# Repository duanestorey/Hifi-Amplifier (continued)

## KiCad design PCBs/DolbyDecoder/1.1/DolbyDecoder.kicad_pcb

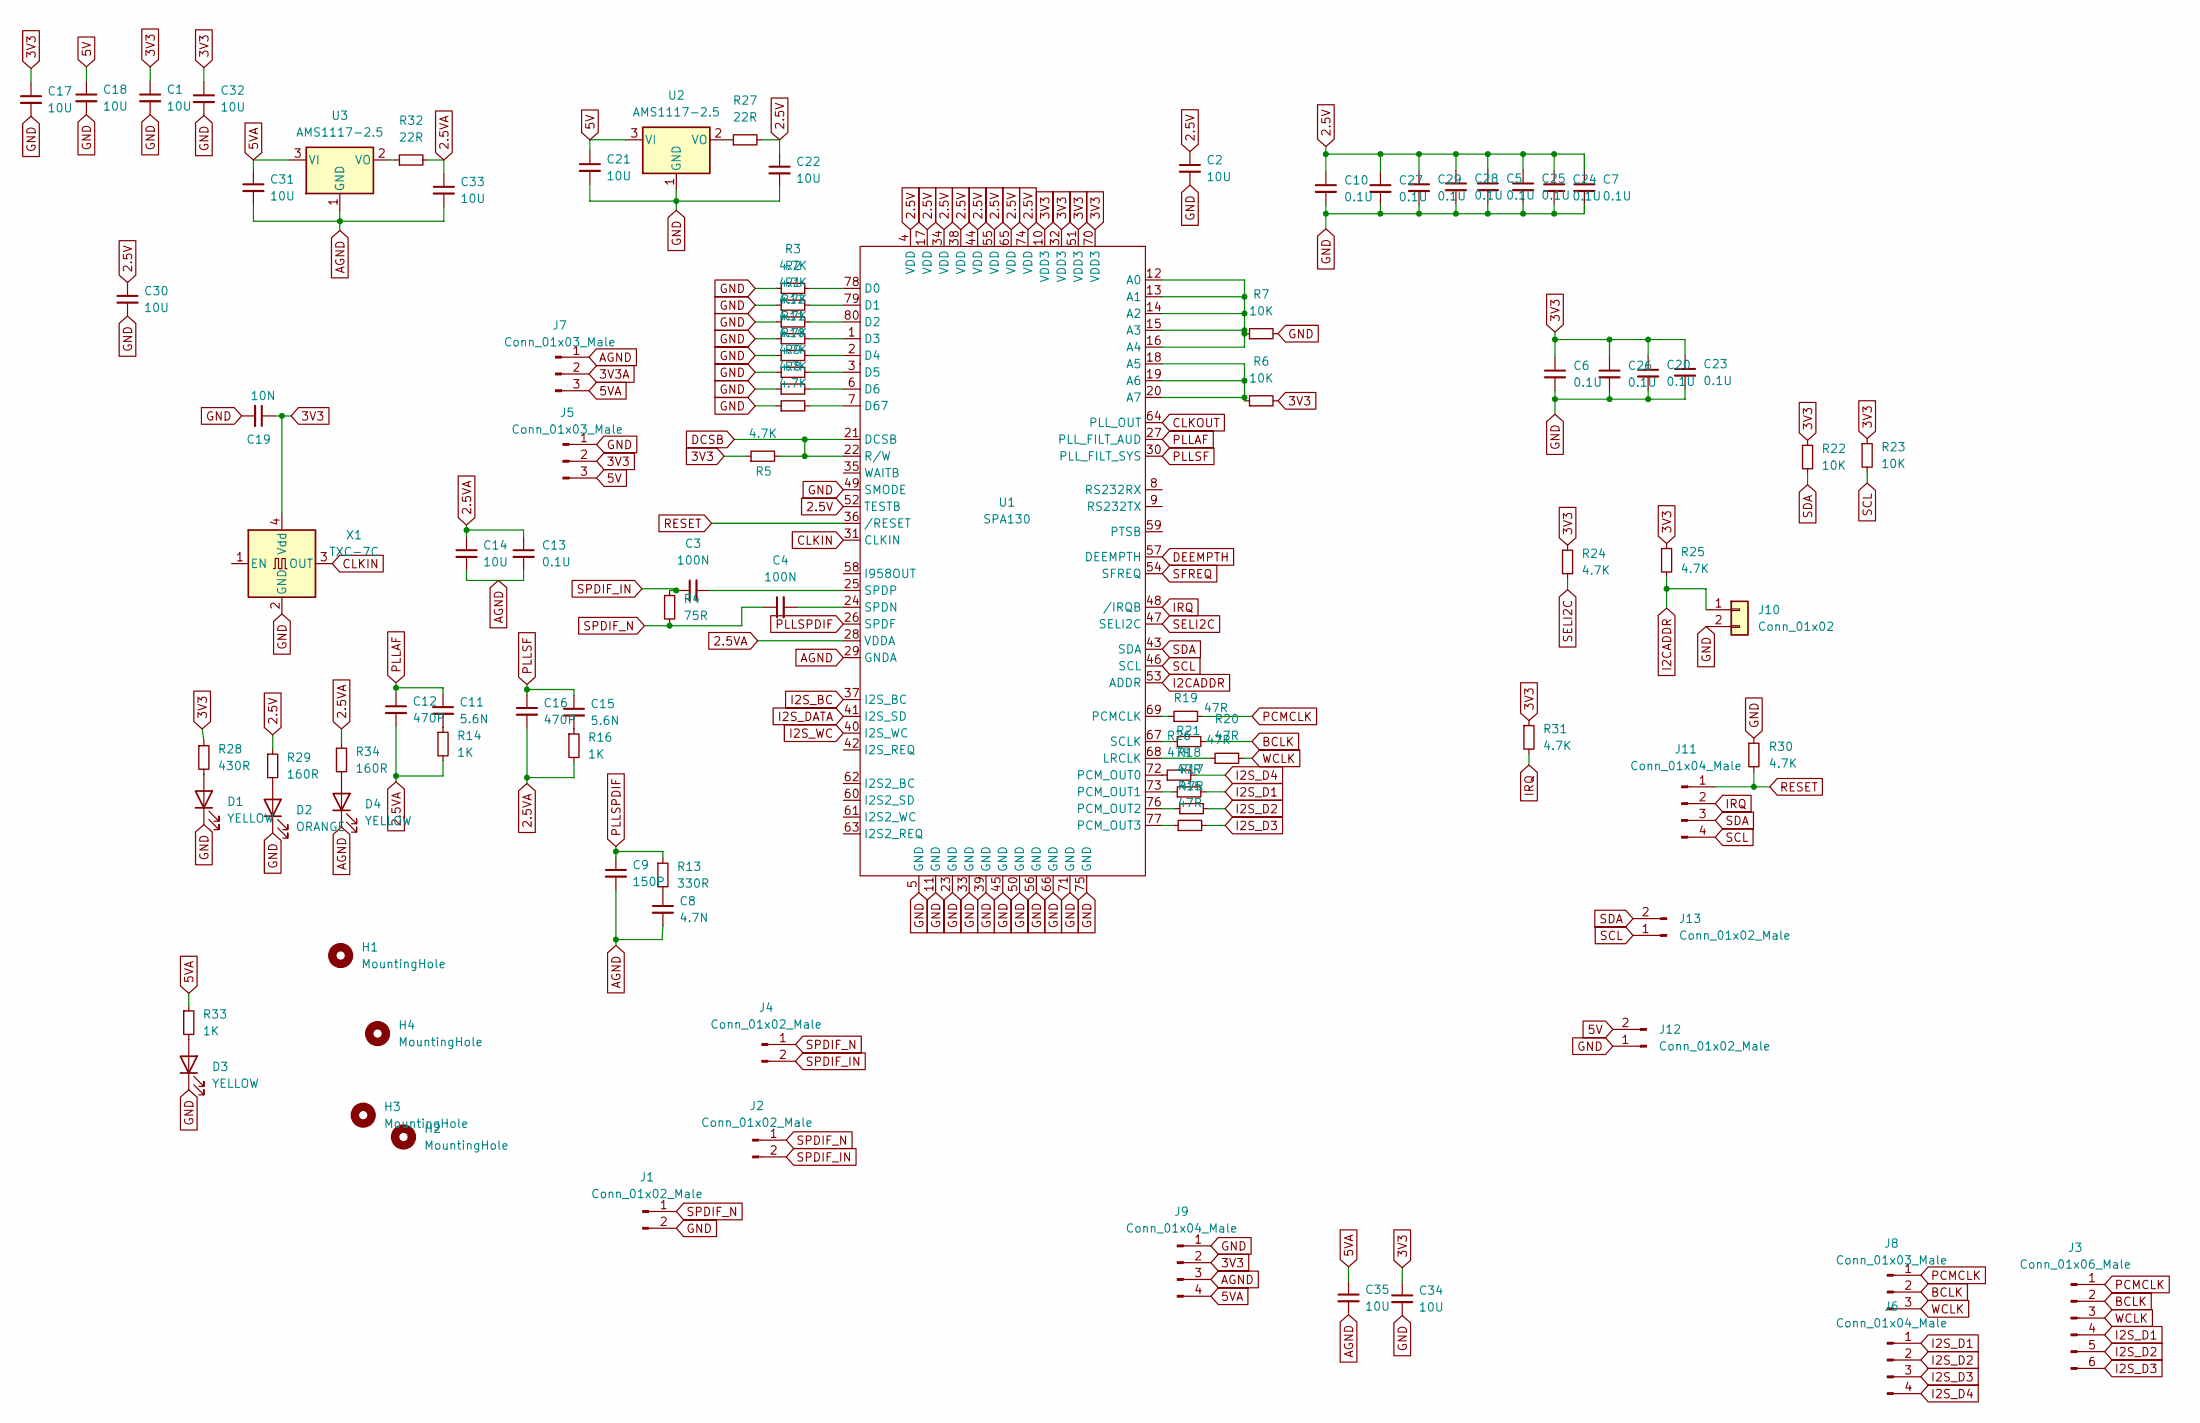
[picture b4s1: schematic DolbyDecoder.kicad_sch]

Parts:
C1, C2, C17, C18, C22, C30, C32, C33, C34, C35: 10U; C_1206_3216Metric_Pad1.33x1.80mm_HandSolder
C3, C4: 100N; C_0805_2012Metric_Pad1.18x1.45mm_HandSolder
C5, C6, C7, C10, C13, C20, C23, C24, C25, C26, C27, C28, C29: 0.1U; C_0603_1608Metric_Pad1.08x0.95mm_HandSolder
C8: 4.7N; C_0805_2012Metric_Pad1.18x1.45mm_HandSolder
C9: 150P; C_0805_2012Metric_Pad1.18x1.45mm_HandSolder
C11, C15: 5.6N; C_0805_2012Metric_Pad1.18x1.45mm_HandSolder
C12, C16: 470P; C_0805_2012Metric_Pad1.18x1.45mm_HandSolder
C14, C21, C31: 10U; C_0805_2012Metric_Pad1.18x1.45mm_HandSolder
C19: 10N; C_0603_1608Metric_Pad1.08x0.95mm_HandSolder
D1, D3, D4: YELLOW; LED_0805_2012Metric_Pad1.15x1.40mm_HandSolder
D2: ORANGE; LED_0805_2012Metric_Pad1.15x1.40mm_HandSolder
H1, H2, H3, H4: MountingHole; MountingHole_3.2mm_M3
J1, J2: Conn_01x02_Male; PinHeader_1x02_P2.54mm_Vertical
J3: Conn_01x06_Male; PinHeader_1x06_P2.54mm_Vertical
J4, J12, J13: Conn_01x02_Male; JST_PH_B2B-PH-K_1x02_P2.00mm_Vertical
J5, J7, J8: Conn_01x03_Male; JST_PH_B3B-PH-K_1x03_P2.00mm_Vertical
J6, J9, J11: Conn_01x04_Male; JST_PH_B4B-PH-K_1x04_P2.00mm_Vertical
J10: Conn_01x02; PinHeader_1x02_P2.54mm_Vertical
R1, R2, R3, R5, R8, R9, R10, R11, R12, R24, R25, R30, R31: 4.7K; R_0603_1608Metric_Pad0.98x0.95mm_HandSolder
R4: 75R; R_0603_1608Metric_Pad0.98x0.95mm_HandSolder
R6, R7, R22, R23: 10K; R_0603_1608Metric_Pad0.98x0.95mm_HandSolder
R13: 330R; R_0603_1608Metric_Pad0.98x0.95mm_HandSolder
R14, R16, R33: 1K; R_0603_1608Metric_Pad0.98x0.95mm_HandSolder
R15, R17, R18, R19, R20, R21, R26: 47R; R_0805_2012Metric_Pad1.20x1.40mm_HandSolder
R27, R32: 22R; R_0805_2012Metric_Pad1.20x1.40mm_HandSolder
R28: 430R; R_0603_1608Metric_Pad0.98x0.95mm_HandSolder
R29, R34: 160R; R_0603_1608Metric_Pad0.98x0.95mm_HandSolder
U1: SPA130; LQFP-80_14x14mm_P0.65mm
U2, U3: AMS1117-2.5; SOT-223
X1: TXC-7C; Oscillator_SMD_EuroQuartz_XO32-4Pin_3.2x2.5mm_HandSoldering

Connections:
2.5V: C2.1, C5.1, C7.1, C10.1, C22.1, C24.1, C25.1, C27.1, C28.1, C29.1, C30.1, R27.2, R29.1, U1.4 (VDD), U1.17 (VDD), U1.34 (VDD), U1.38 (VDD), U1.44 (VDD), U1.52 (TESTB), U1.55 (VDD), U1.65 (VDD), U1.74 (VDD)
2.5VA: C12.2, C13.1, C14.1, C16.2, C33.1, R14.2, R16.2, R32.2, R34.1, U1.28 (VDDA)
3V3: C1.1, C6.1, C17.1, C19.1, C20.1, C23.1, C26.1, C32.1, C34.1, J5.2, J9.2, R5.1, R6.2, R22.1, R23.1, R24.1, R25.1, R28.1, R31.1, U1.10 (VDD3), U1.32 (VDD3), U1.51 (VDD3), U1.70 (VDD3), X1.4 (Vdd)
3V3A: J7.2
5V: C18.1, C21.1, J5.3, J12.2, U2.3 (VI)
5VA: C31.1, C35.1, J7.3, J9.4, R33.1, U3.3 (VI)
AGND: C8.2, C9.2, C13.2, C14.2, C31.2, C33.2, C35.2, D4.1 (K), J7.1, J9.3, U1.29 (GNDA), U3.1 (GND)
BCLK: J3.2, J8.2, R21.2
CLKIN: U1.31 (CLKIN), X1.3 (OUT)
CLKOUT: U1.64 (PLL_OUT)
DCSB: R5.2, U1.21 (DCSB), U1.22 (R/W)
DEEMPTH: U1.57 (DEEMPTH)
GND: C1.2, C2.2, C5.2, C6.2, C7.2, C10.2, C17.2, C18.2, C19.2, C20.2, C21.2, C22.2, C23.2, C24.2, C25.2, C26.2, C27.2, C28.2, C29.2, C30.2, C32.2, C34.2, D1.1 (K), D2.1 (K), D3.1 (K), J1.2, J5.1, J9.1, J10.2, J12.1, R1.1, R2.1, R3.1, R7.2, R8.1, R9.1, R10.1, R11.1, R12.1, R30.1, U1.5 (GND), U1.11 (GND), U1.23 (GND), U1.33 (GND), U1.39 (GND), U1.45 (GND), U1.49 (SMODE), U1.50 (GND), U1.56 (GND), U1.66 (GND), U1.71 (GND), U1.75 (GND), U2.1 (GND), X1.2 (GND)
I2CADDR: J10.1, R25.2, U1.53 (ADDR)
I2S_BC: U1.37 (I2S_BC)
I2S_D1: J3.4, J6.1, R18.2
I2S_D2: J3.5, J6.2, R17.2
I2S_D3: J3.6, J6.3, R15.2
I2S_D4: J6.4, R26.2
I2S_DATA: U1.41 (I2S_SD)
I2S_WC: U1.40 (I2S_WC)
IRQ: J11.2, R31.2, U1.48 (/IRQB)
unnamed: C8.1, R13.2
unnamed: C11.2, R14.1
unnamed: C15.2, R16.1
unnamed: D1.2 (A), R28.2
unnamed: D2.2 (A), R29.2
unnamed: D3.2 (A), R33.2
unnamed: D4.2 (A), R34.2
unnamed: R7.1, U1.12 (A0), U1.13 (A1), U1.14 (A2), U1.15 (A3), U1.16 (A4)
unnamed: R6.1, U1.18 (A5), U1.19 (A6), U1.20 (A7)
unnamed: R3.2, U1.78 (D0)
unnamed: R2.2, U1.79 (D1)
unnamed: R1.2, U1.80 (D2)
unnamed: R12.2, U1.1 (D3)
unnamed: R11.2, U1.2 (D4)
unnamed: R10.2, U1.3 (D5)
unnamed: R9.2, U1.6 (D6)
unnamed: R8.2, U1.7 (D67)
unnamed: R20.1, U1.68 (LRCLK)
unnamed: R19.1, U1.69 (PCMCLK)
unnamed: R26.1, U1.72 (PCM_OUT0)
unnamed: R18.1, U1.73 (PCM_OUT1)
unnamed: R17.1, U1.76 (PCM_OUT2)
unnamed: R15.1, U1.77 (PCM_OUT3)
unnamed: R21.1, U1.67 (SCLK)
unnamed: C4.2, U1.24 (SPDN)
unnamed: C3.2, U1.25 (SPDP)
unnamed: R27.1, U2.2 (VO)
unnamed: R32.1, U3.2 (VO)
PCMCLK: J3.1, J8.1, R19.2
PLLAF: C11.1, C12.1, U1.27 (PLL_FILT_AUD)
PLLSF: C15.1, C16.1, U1.30 (PLL_FILT_SYS)
PLLSPDIF: C9.1, R13.1, U1.26 (SPDF)
RESET: J11.1, R30.2, U1.36 (/RESET)
SCL: J11.4, J13.1, R23.2, U1.46 (SCL)
SDA: J11.3, J13.2, R22.2, U1.43 (SDA)
SELI2C: R24.2, U1.47 (SELI2C)
SFREQ: U1.54 (SFREQ)
SPDIF_IN: C3.1, J2.2, J4.2, R4.1
SPDIF_N: C4.1, J1.1, J2.1, J4.1, R4.2
WCLK: J3.3, J8.3, R20.2

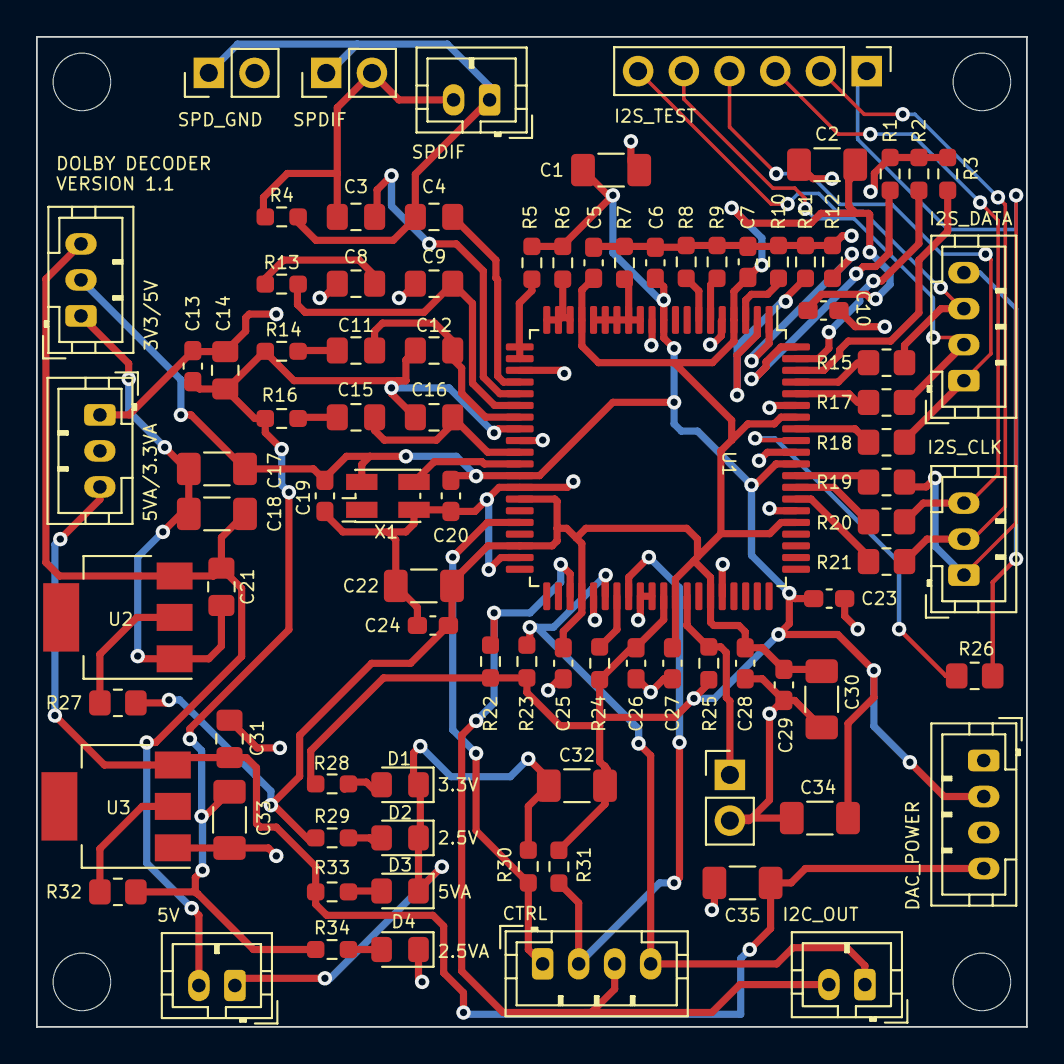
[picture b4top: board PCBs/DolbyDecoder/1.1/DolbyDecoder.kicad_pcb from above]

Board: 2 copper layers, 55.0 x 55.0 mm, 94 parts (0 on the bottom side), 55 nets.

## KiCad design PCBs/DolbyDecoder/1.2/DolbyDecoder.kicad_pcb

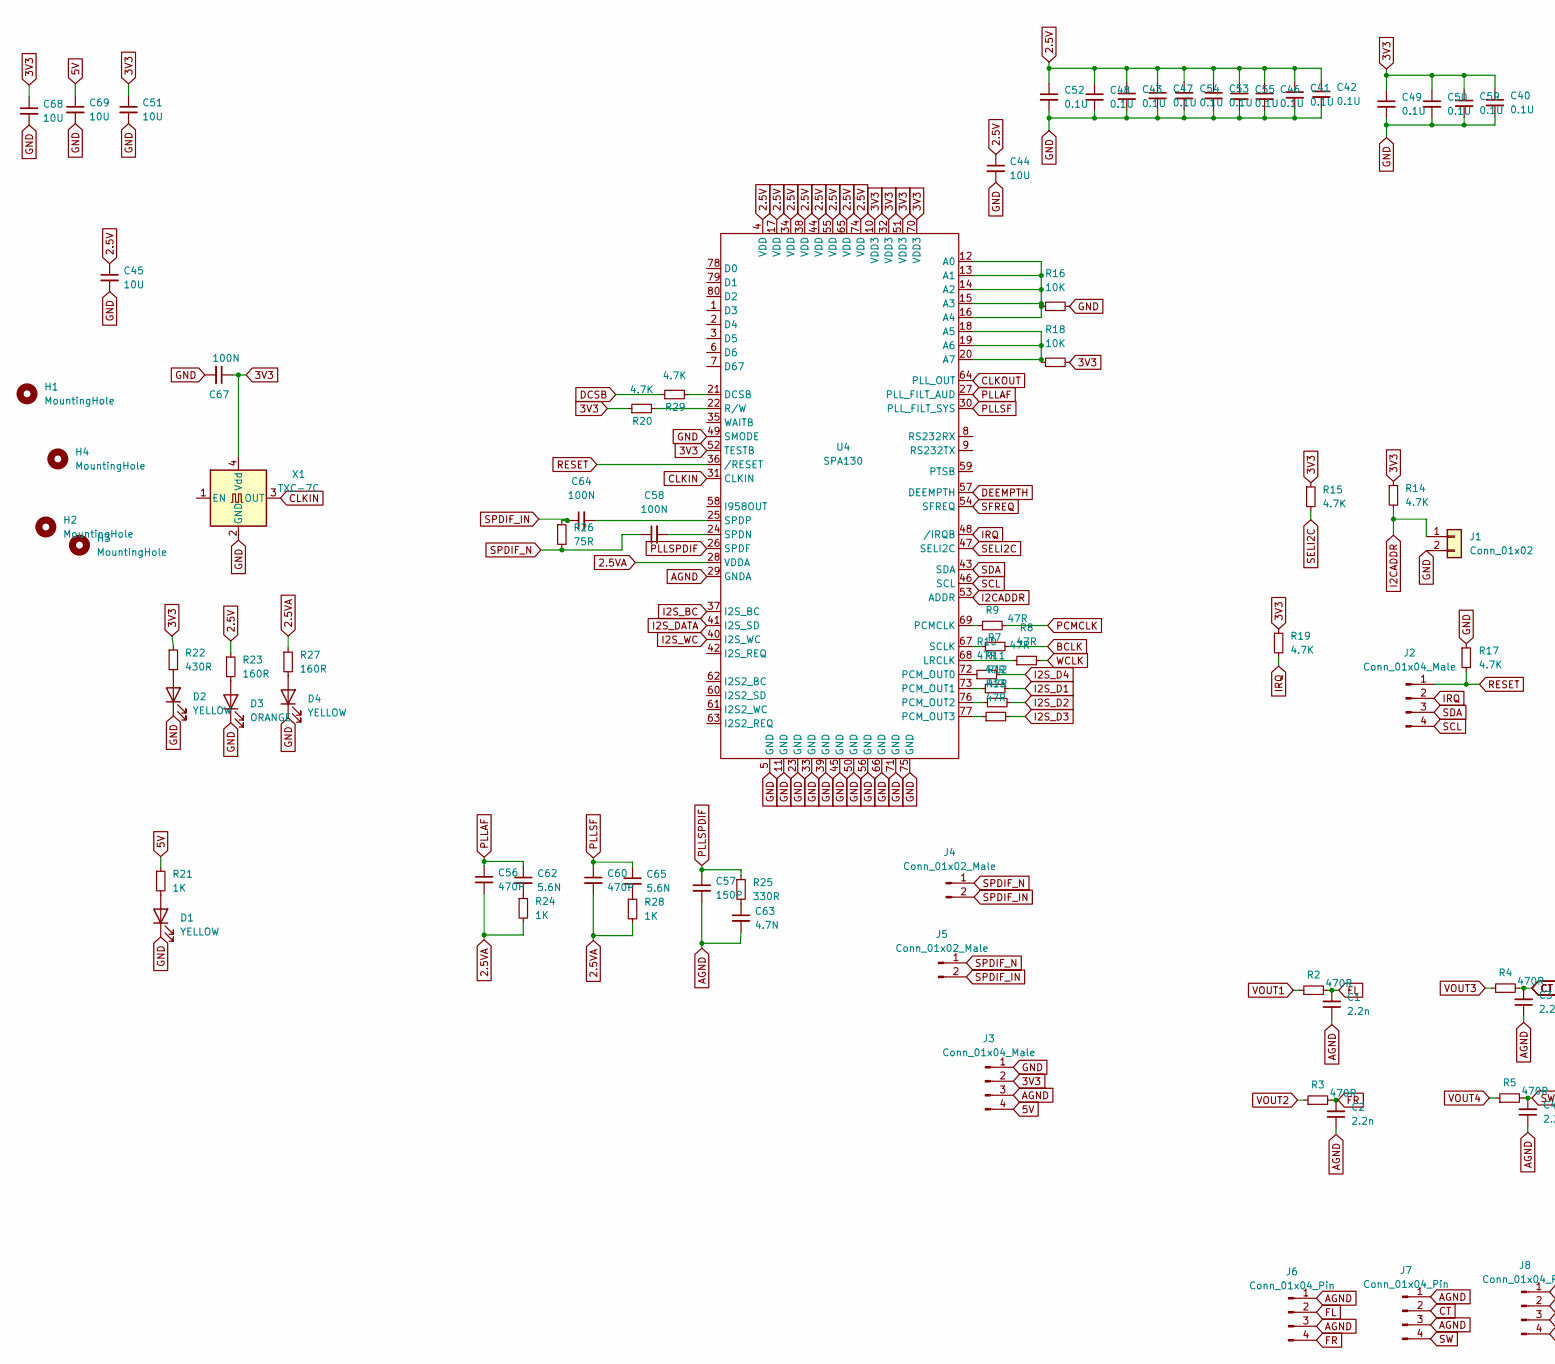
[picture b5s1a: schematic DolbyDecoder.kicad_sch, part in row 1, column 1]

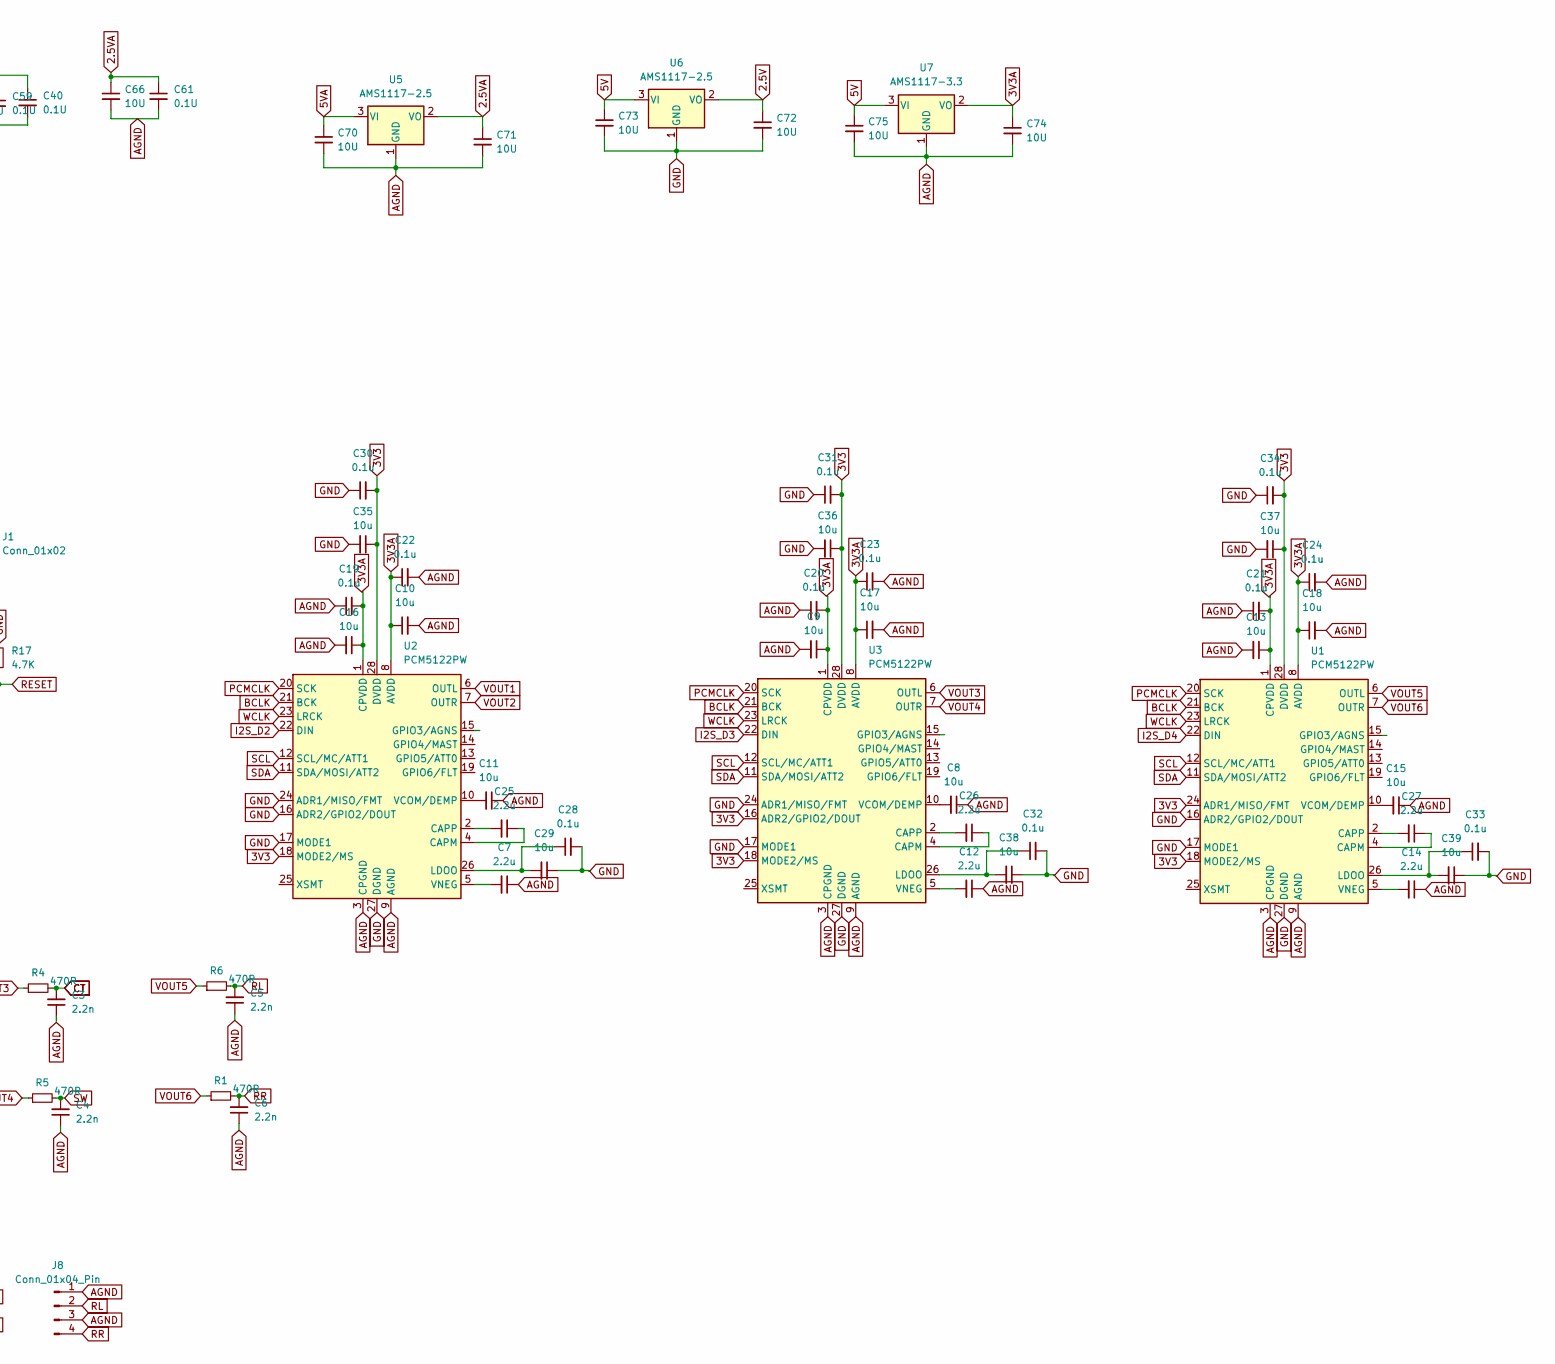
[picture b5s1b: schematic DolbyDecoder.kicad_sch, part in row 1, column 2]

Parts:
C1, C2, C3, C4, C5, C6: 2.2n; C_1206_3216Metric_Pad1.33x1.80mm_HandSolder
C7, C12, C14, C25, C26, C27: 2.2u; C_1206_3216Metric_Pad1.33x1.80mm_HandSolder
C8, C9, C10, C11, C13, C15, C16, C17, C18, C29, C35, C36, C37, C38, C39: 10u; C_1206_3216Metric_Pad1.33x1.80mm_HandSolder
C19, C20, C21, C22, C23, C24, C28, C30, C31, C32, C33, C34: 0.1u; C_0805_2012Metric_Pad1.18x1.45mm_HandSolder
C40, C41, C42, C43, C46, C47, C48, C49, C50, C52, C53, C54, C55, C59, C61: 0.1U; C_0603_1608Metric_Pad1.08x0.95mm_HandSolder
C44, C45, C51, C68, C69, C70, C71, C72, C73, C74, C75: 10U; C_1206_3216Metric_Pad1.33x1.80mm_HandSolder
C56, C60: 470P; C_0805_2012Metric_Pad1.18x1.45mm_HandSolder
C57: 150P; C_0805_2012Metric_Pad1.18x1.45mm_HandSolder
C58, C64: 100N; C_0805_2012Metric_Pad1.18x1.45mm_HandSolder
C62, C65: 5.6N; C_0805_2012Metric_Pad1.18x1.45mm_HandSolder
C63: 4.7N; C_0805_2012Metric_Pad1.18x1.45mm_HandSolder
C66: 10U; C_0805_2012Metric_Pad1.18x1.45mm_HandSolder
C67: 100N; C_0603_1608Metric_Pad1.08x0.95mm_HandSolder
D1, D2, D4: YELLOW; LED_0805_2012Metric_Pad1.15x1.40mm_HandSolder
D3: ORANGE; LED_0805_2012Metric_Pad1.15x1.40mm_HandSolder
H1, H2, H3, H4: MountingHole; MountingHole_3.2mm_M3
J1: Conn_01x02; PinHeader_1x02_P2.54mm_Vertical
J2, J3: Conn_01x04_Male; JST_PH_B4B-PH-K_1x04_P2.00mm_Vertical
J4: Conn_01x02_Male; JST_PH_B2B-PH-K_1x02_P2.00mm_Vertical
J5: Conn_01x02_Male; PinHeader_1x02_P2.54mm_Vertical
J6, J7, J8: Conn_01x04_Pin; JST_PH_B4B-PH-K_1x04_P2.00mm_Vertical
R1, R2, R3, R4, R5, R6: 470R; R_1206_3216Metric_Pad1.30x1.75mm_HandSolder
R7, R8, R9, R10, R11, R12, R13: 47R; R_0805_2012Metric_Pad1.20x1.40mm_HandSolder
R14, R15, R17, R19, R20, R29: 4.7K; R_0603_1608Metric_Pad0.98x0.95mm_HandSolder
R16, R18: 10K; R_0603_1608Metric_Pad0.98x0.95mm_HandSolder
R21, R24, R28: 1K; R_0603_1608Metric_Pad0.98x0.95mm_HandSolder
R22: 430R; R_0603_1608Metric_Pad0.98x0.95mm_HandSolder
R23, R27: 160R; R_0603_1608Metric_Pad0.98x0.95mm_HandSolder
R25: 330R; R_0603_1608Metric_Pad0.98x0.95mm_HandSolder
R26: 75R; R_0603_1608Metric_Pad0.98x0.95mm_HandSolder
U1, U2, U3: PCM5122PW; TSSOP-28_4.4x9.7mm_P0.65mm
U4: SPA130; LQFP-80_14x14mm_P0.65mm
U5, U6: AMS1117-2.5; SOT-223
U7: AMS1117-3.3; SOT-223
X1: TXC-7C; Oscillator_SMD_EuroQuartz_XO32-4Pin_3.2x2.5mm_HandSoldering

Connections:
2.5V: C41.1, C42.1, C43.1, C44.1, C45.1, C46.1, C47.1, C48.1, C52.1, C53.1, C54.1, C55.1, C72.1, R23.1, U4.4 (VDD), U4.17 (VDD), U4.34 (VDD), U4.38 (VDD), U4.44 (VDD), U4.55 (VDD), U4.65 (VDD), U4.74 (VDD), U6.2 (VO)
2.5VA: C56.2, C60.2, C61.1, C66.1, C71.1, R24.2, R27.1, R28.2, U4.28 (VDDA), U5.2 (VO)
3V3: C30.2, C31.2, C34.2, C35.1, C36.1, C37.1, C40.1, C49.1, C50.1, C51.1, C59.1, C67.1, C68.1, J3.2, R14.1, R15.1, R18.2, R19.1, R20.1, R22.1, U1.18 (MODE2/MS), U1.24 (ADR1/MISO/FMT), U1.28 (DVDD), U2.18 (MODE2/MS), U2.28 (DVDD), U3.16 (ADR2/GPIO2/DOUT), U3.18 (MODE2/MS), U3.28 (DVDD), U4.10 (VDD3), U4.32 (VDD3), U4.51 (VDD3), U4.52 (TESTB), U4.70 (VDD3), X1.4 (Vdd)
3V3A: C9.1, C10.1, C13.1, C16.1, C17.1, C18.1, C19.2, C20.2, C21.2, C22.1, C23.1, C24.1, C74.1, U1.1 (CPVDD), U1.8 (AVDD), U2.1 (CPVDD), U2.8 (AVDD), U3.1 (CPVDD), U3.8 (AVDD), U7.2 (VO)
5V: C69.1, C73.1, C75.1, J3.4, R21.1, U6.3 (VI), U7.3 (VI)
5VA: C70.1, U5.3 (VI)
AGND: C1.1, C2.1, C3.1, C4.1, C5.1, C6.1, C7.1, C8.1, C9.2, C10.2, C11.1, C12.1, C13.2, C14.1, C15.1, C16.2, C17.2, C18.2, C19.1, C20.1, C21.1, C22.2, C23.2, C24.2, C57.2, C61.2, C63.2, C66.2, C70.2, C71.2, C74.2, C75.2, J3.3, J6.1, J6.3, J7.1, J7.3, J8.1, J8.3, U1.3 (CPGND), U1.9 (AGND), U2.3 (CPGND), U2.9 (AGND), U3.3 (CPGND), U3.9 (AGND), U4.29 (GNDA), U5.1 (GND), U7.1 (GND)
BCLK: R7.2, U1.21 (BCK), U2.21 (BCK), U3.21 (BCK)
CLKIN: U4.31 (CLKIN), X1.3 (OUT)
CLKOUT: U4.64 (PLL_OUT)
CT: C3.2, J7.2, R4.2
DCSB: R29.1
DEEMPTH: U4.57 (DEEMPTH)
FL: C1.2, J6.2, R2.2
FR: C2.2, J6.4, R3.2
GND: C28.2, C29.1, C30.1, C31.1, C32.2, C33.2, C34.1, C35.2, C36.2, C37.2, C38.1, C39.1, C40.2, C41.2, C42.2, C43.2, C44.2, C45.2, C46.2, C47.2, C48.2, C49.2, C50.2, C51.2, C52.2, C53.2, C54.2, C55.2, C59.2, C67.2, C68.2, C69.2, C72.2, C73.2, D1.1 (K), D2.1 (K), D3.1 (K), D4.1 (K), J1.2, J3.1, R16.2, R17.1, U1.16 (ADR2/GPIO2/DOUT), U1.17 (MODE1), U1.27 (DGND), U2.16 (ADR2/GPIO2/DOUT), U2.17 (MODE1), U2.24 (ADR1/MISO/FMT), U2.27 (DGND), U3.17 (MODE1), U3.24 (ADR1/MISO/FMT), U3.27 (DGND), U4.5 (GND), U4.11 (GND), U4.23 (GND), U4.33 (GND), U4.39 (GND), U4.45 (GND), U4.49 (SMODE), U4.50 (GND), U4.56 (GND), U4.66 (GND), U4.71 (GND), U4.75 (GND), U6.1 (GND), X1.2 (GND)
I2CADDR: J1.1, R14.2, U4.53 (ADDR)
I2S_BC: U4.37 (I2S_BC)
I2S_D1: R11.2
I2S_D2: R12.2, U2.22 (DIN)
I2S_D3: R13.2, U3.22 (DIN)
I2S_D4: R10.2, U1.22 (DIN)
I2S_DATA: U4.41 (I2S_SD)
I2S_WC: U4.40 (I2S_WC)
IRQ: J2.2, R19.2, U4.48 (/IRQB)
unnamed: C62.2, R24.1
unnamed: C63.1, R25.2
unnamed: C65.2, R28.1
unnamed: D1.2 (A), R21.2
unnamed: D2.2 (A), R22.2
unnamed: D3.2 (A), R23.2
unnamed: D4.2 (A), R27.2
unnamed: C27.1, U1.4 (CAPM)
unnamed: C27.2, U1.2 (CAPP)
unnamed: C33.1, C39.2, U1.26 (LDOO)
unnamed: C15.2, U1.10 (VCOM/DEMP)
unnamed: C14.2, U1.5 (VNEG)
unnamed: C25.1, U2.4 (CAPM)
unnamed: C25.2, U2.2 (CAPP)
unnamed: C28.1, C29.2, U2.26 (LDOO)
unnamed: C11.2, U2.10 (VCOM/DEMP)
unnamed: C7.2, U2.5 (VNEG)
unnamed: C26.1, U3.4 (CAPM)
unnamed: C26.2, U3.2 (CAPP)
unnamed: C32.1, C38.2, U3.26 (LDOO)
unnamed: C8.2, U3.10 (VCOM/DEMP)
unnamed: C12.2, U3.5 (VNEG)
unnamed: R16.1, U4.12 (A0), U4.13 (A1), U4.14 (A2), U4.15 (A3), U4.16 (A4)
unnamed: R18.1, U4.18 (A5), U4.19 (A6), U4.20 (A7)
unnamed: R29.2, U4.21 (DCSB)
unnamed: R8.1, U4.68 (LRCLK)
unnamed: R9.1, U4.69 (PCMCLK)
unnamed: R10.1, U4.72 (PCM_OUT0)
unnamed: R11.1, U4.73 (PCM_OUT1)
unnamed: R12.1, U4.76 (PCM_OUT2)
unnamed: R13.1, U4.77 (PCM_OUT3)
unnamed: R20.2, U4.22 (R/W)
unnamed: R7.1, U4.67 (SCLK)
unnamed: C58.2, U4.24 (SPDN)
unnamed: C64.2, U4.25 (SPDP)
PCMCLK: R9.2, U1.20 (SCK), U2.20 (SCK), U3.20 (SCK)
PLLAF: C56.1, C62.1, U4.27 (PLL_FILT_AUD)
PLLSF: C60.1, C65.1, U4.30 (PLL_FILT_SYS)
PLLSPDIF: C57.1, R25.1, U4.26 (SPDF)
RESET: J2.1, R17.2, U4.36 (/RESET)
RL: C5.2, J8.2, R6.2
RR: C6.2, J8.4, R1.2
SCL: J2.4, U1.12 (SCL/MC/ATT1), U2.12 (SCL/MC/ATT1), U3.12 (SCL/MC/ATT1), U4.46 (SCL)
SDA: J2.3, U1.11 (SDA/MOSI/ATT2), U2.11 (SDA/MOSI/ATT2), U3.11 (SDA/MOSI/ATT2), U4.43 (SDA)
SELI2C: R15.2, U4.47 (SELI2C)
SFREQ: U4.54 (SFREQ)
SPDIF_IN: C64.1, J4.2, J5.2, R26.1
SPDIF_N: C58.1, J4.1, J5.1, R26.2
SW: C4.2, J7.4, R5.2
VOUT1: R2.1, U2.6 (OUTL)
VOUT2: R3.1, U2.7 (OUTR)
VOUT3: R4.1, U3.6 (OUTL)
VOUT4: R5.1, U3.7 (OUTR)
VOUT5: R6.1, U1.6 (OUTL)
VOUT6: R1.1, U1.7 (OUTR)
WCLK: R8.2, U1.23 (LRCK), U2.23 (LRCK), U3.23 (LRCK)

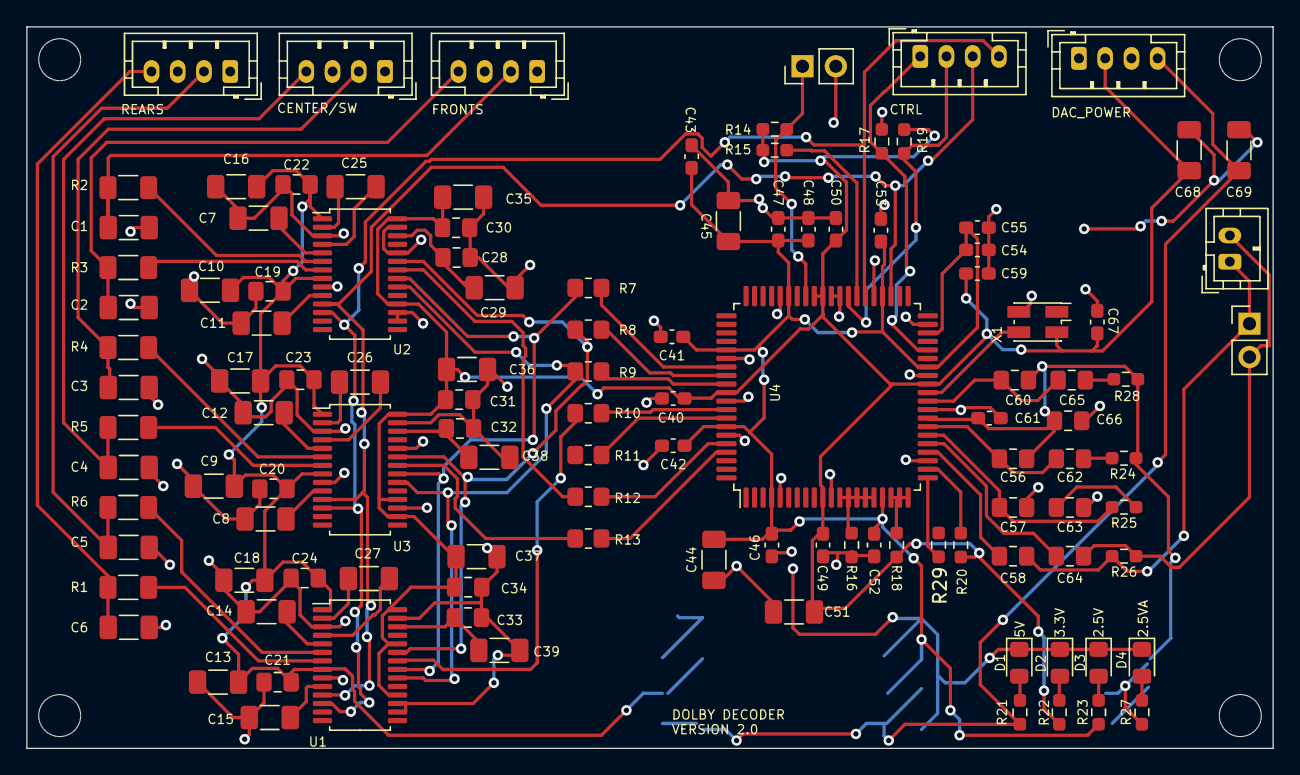
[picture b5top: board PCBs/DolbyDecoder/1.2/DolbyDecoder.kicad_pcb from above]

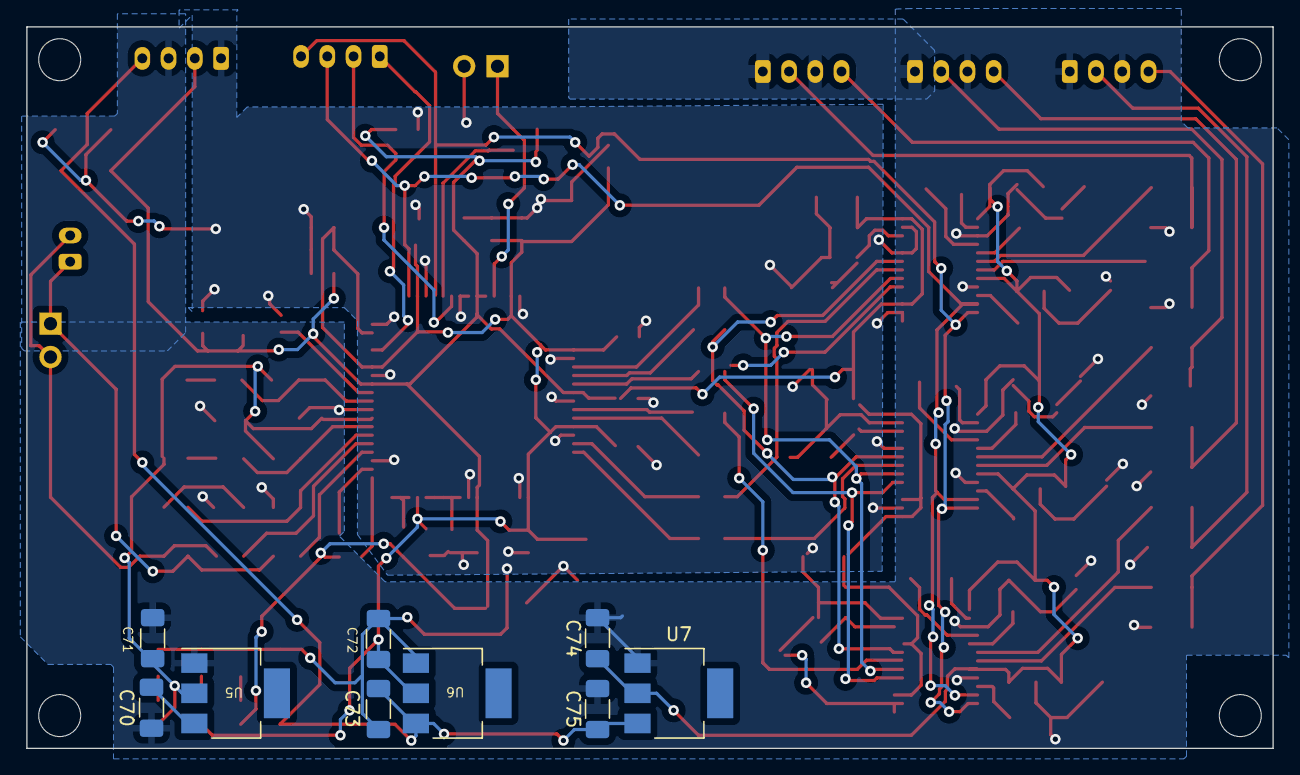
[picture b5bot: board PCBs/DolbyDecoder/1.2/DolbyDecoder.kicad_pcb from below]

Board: 2 copper layers, 95.0 x 55.0 mm, 128 parts (9 on the bottom side), 73 nets.
